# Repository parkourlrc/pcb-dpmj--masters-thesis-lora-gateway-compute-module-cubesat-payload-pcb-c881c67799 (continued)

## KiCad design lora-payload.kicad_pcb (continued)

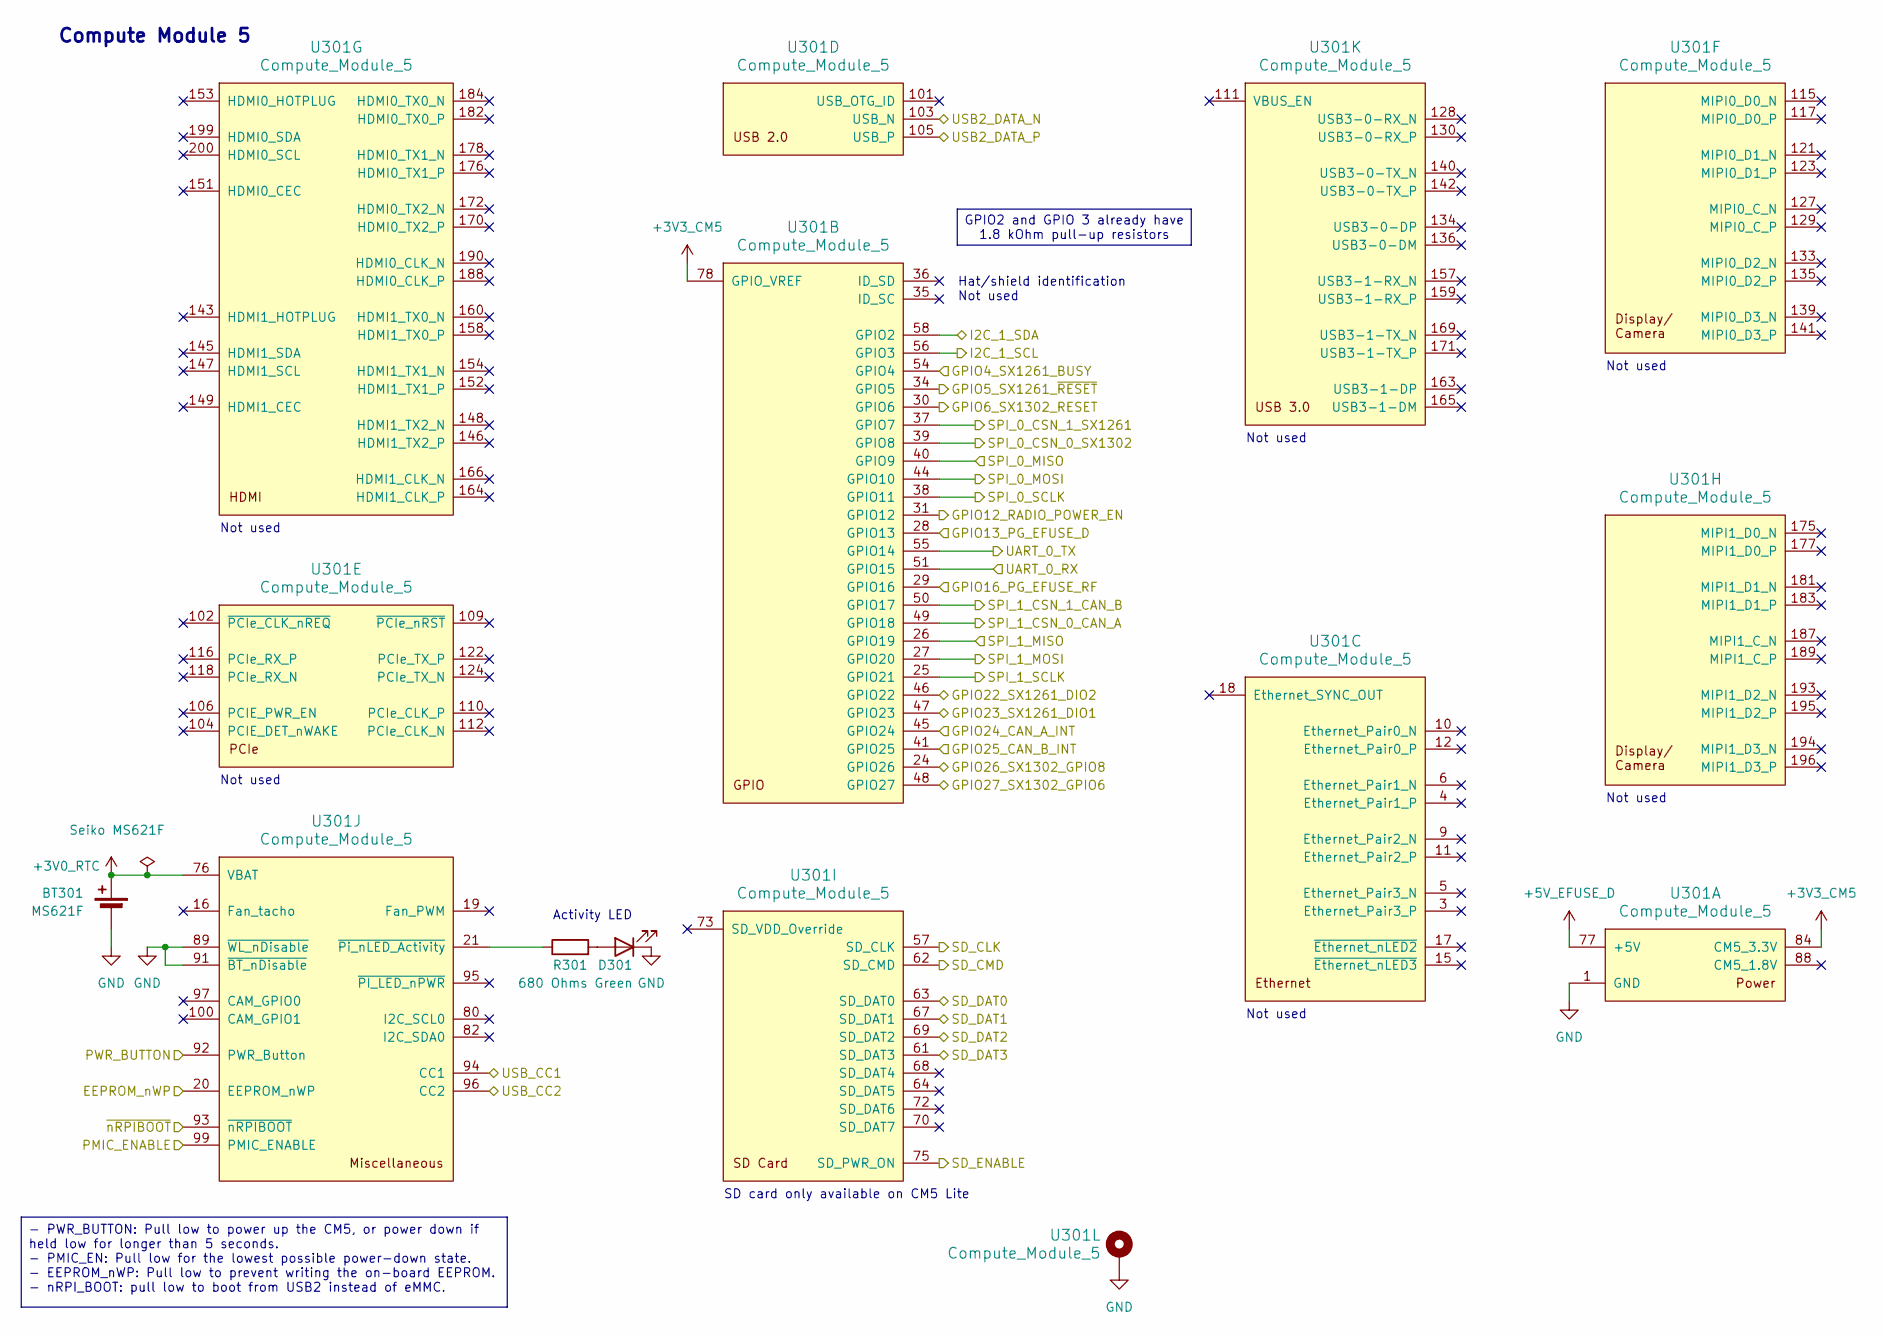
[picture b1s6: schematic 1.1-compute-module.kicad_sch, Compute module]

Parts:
BT301: Seiko MS621F; BatteryHolder_Seiko_MS621F; PartNumber MS621F
D301: Green; LED_0402_1005Metric
R301: 680 Ohms; R_0402_1005Metric
U301: Compute_Module_5; CM5

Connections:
+3V0_RTC: BT301.1 (+), U301.76 (VBAT)
+3V3_CM5: U301.78 (GPIO_VREF), U301.84 (CM5_3.3V), U301.86 (CM5_3.3V)
+5V_EFUSE_D: U301.77 (+5V), U301.79 (+5V), U301.81 (+5V), U301.83 (+5V), U301.85 (+5V), U301.87 (+5V); also elsewhere on the board
/1.0-digital/1.1-compute-module/EEPROM_nWP: U301.20 (EEPROM_nWP); also elsewhere on the board
/1.0-digital/1.1-compute-module/GPIO24_CAN_A_INT: U301.45 (GPIO24); also elsewhere on the board
/1.0-digital/1.1-compute-module/GPIO25_CAN_B_INT: U301.41 (GPIO25); also elsewhere on the board
/1.0-digital/1.1-compute-module/PMIC_ENABLE: U301.99 (PMIC_ENABLE); also elsewhere on the board
/1.0-digital/1.1-compute-module/SD_CLK: U301.57 (SD_CLK); also elsewhere on the board
/1.0-digital/1.1-compute-module/SD_CMD: U301.62 (SD_CMD); also elsewhere on the board
/1.0-digital/1.1-compute-module/SD_DAT0: U301.63 (SD_DAT0); also elsewhere on the board
/1.0-digital/1.1-compute-module/SD_DAT1: U301.67 (SD_DAT1); also elsewhere on the board
/1.0-digital/1.1-compute-module/SD_DAT2: U301.69 (SD_DAT2); also elsewhere on the board
/1.0-digital/1.1-compute-module/SD_DAT3: U301.61 (SD_DAT3); also elsewhere on the board
/1.0-digital/1.1-compute-module/SD_ENABLE: U301.75 (SD_PWR_ON); also elsewhere on the board
/1.0-digital/1.1-compute-module/SPI_1_CSN_0_CAN_A: U301.49 (GPIO18); also elsewhere on the board
/1.0-digital/1.1-compute-module/SPI_1_CSN_1_CAN_B: U301.50 (GPIO17); also elsewhere on the board
/1.0-digital/1.1-compute-module/SPI_1_MISO: U301.26 (GPIO19); also elsewhere on the board
/1.0-digital/1.1-compute-module/SPI_1_MOSI: U301.27 (GPIO20); also elsewhere on the board
/1.0-digital/1.1-compute-module/SPI_1_SCLK: U301.25 (GPIO21); also elsewhere on the board
/1.0-digital/1.1-compute-module/UART_0_RX: U301.51 (GPIO15); also elsewhere on the board
/1.0-digital/1.1-compute-module/UART_0_TX: U301.55 (GPIO14); also elsewhere on the board
/1.0-digital/1.1-compute-module/~nRPIBOOT: U301.93 (~nRPIBOOT); also elsewhere on the board
/1.0-digital/1.3-usb/USB2_DATA_N: U301.103 (USB_N); also elsewhere on the board
/1.0-digital/1.3-usb/USB2_DATA_P: U301.105 (USB_P); also elsewhere on the board
/1.0-digital/1.3-usb/USB_CC1: U301.94 (CC1); also elsewhere on the board
/1.0-digital/1.3-usb/USB_CC2: U301.96 (CC2); also elsewhere on the board
/1.0-digital/CM5_GPIO4_SX1261_BUSY: U301.54 (GPIO4); also elsewhere on the board
/1.0-digital/CM5_GPIO5_SX1261_~RESET: U301.34 (GPIO5); also elsewhere on the board
/1.0-digital/CM5_GPIO6_SX1302_RESET: U301.30 (GPIO6); also elsewhere on the board
/1.0-digital/CM5_GPIO12_RADIO_POWER_EN: U301.31 (GPIO12); also elsewhere on the board
/1.0-digital/CM5_GPIO22_SX1261_DIO2: U301.46 (GPIO22); also elsewhere on the board
/1.0-digital/CM5_GPIO23_SX1261_DIO1: U301.47 (GPIO23); also elsewhere on the board
/1.0-digital/CM5_GPIO26_SX1302_GPIO8: U301.24 (GPIO26); also elsewhere on the board
/1.0-digital/CM5_GPIO27_SX1302_GPIO6: U301.48 (GPIO27); also elsewhere on the board
/1.0-digital/CM5_SPI_0_CSN_0_SX1302: U301.39 (GPIO8); also elsewhere on the board
/1.0-digital/CM5_SPI_0_CSN_1_SX1261: U301.37 (GPIO7); also elsewhere on the board
/1.0-digital/CM5_SPI_0_MISO: U301.40 (GPIO9); also elsewhere on the board
/1.0-digital/CM5_SPI_0_MOSI: U301.44 (GPIO10); also elsewhere on the board
/1.0-digital/CM5_SPI_0_SCLK: U301.38 (GPIO11); also elsewhere on the board
/1.0-digital/I2C.SCL: U301.56 (GPIO3); also elsewhere on the board
/1.0-digital/I2C.SDA: U301.58 (GPIO2); also elsewhere on the board
/1.0-digital/PWR_BUTTON: U301.92 (PWR_Button); also elsewhere on the board
/3.0-power/3.1-efuse/PG_EFD: U301.28 (GPIO13); also elsewhere on the board
/3.0-power/3.1-efuse/PG_EFRF: U301.29 (GPIO16); also elsewhere on the board
GND: BT301.2 (-), D301.1 (K), U301.1 (GND), U301.2 (GND), U301.7 (GND), U301.8 (GND), U301.13 (GND), U301.14 (GND), U301.22 (GND), U301.23 (GND), U301.32 (GND), U301.33 (GND), U301.42 (GND), U301.43 (GND), U301.52 (GND), U301.53 (GND), U301.59 (GND), U301.60 (GND), U301.65 (GND), U301.66 (GND), U301.71 (GND), U301.74 (GND), U301.89 (~WL_nDisable), U301.91 (~BT_nDisable), U301.98 (GND), U301.107 (GND), U301.108 (GND), U301.113 (GND), U301.114 (GND), U301.119 (GND), U301.120 (GND), U301.125 (GND), U301.126 (GND), U301.131 (GND), U301.132 (GND), U301.137 (GND), U301.138 (GND), U301.144 (GND), U301.150 (GND), U301.155 (GND), U301.156 (GND), U301.161 (GND), U301.162 (GND), U301.167 (GND), U301.168 (GND), U301.173 (GND), U301.174 (GND), U301.179 (GND), U301.180 (GND), U301.185 (GND), U301.186 (GND), U301.191 (GND), U301.192 (GND), U301.197 (GND), U301.198 (GND), U301.MH; also elsewhere on the board
unnamed: D301.2 (A), R301.2
unnamed: R301.1, U301.21 (~Pi_nLED_Activity)

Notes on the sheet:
SD card only available on CM5 Lite
Compute Module 5
Not used
Hat/shield identification Not used
Activity LED
- PWR_BUTTON: Pull low to power up the CM5, or power down if held low for longer than 5 seconds. - PMIC_EN: Pull low for the lowest possible power-down state. - EEPROM_nWP: Pull low to prevent writing the on-board EEPROM. - nRPI_BOOT: pull low to boot from USB2 instead of eMMC.
GPIO2 and GPIO 3 already have 1.8 kOhm pull-up resistors

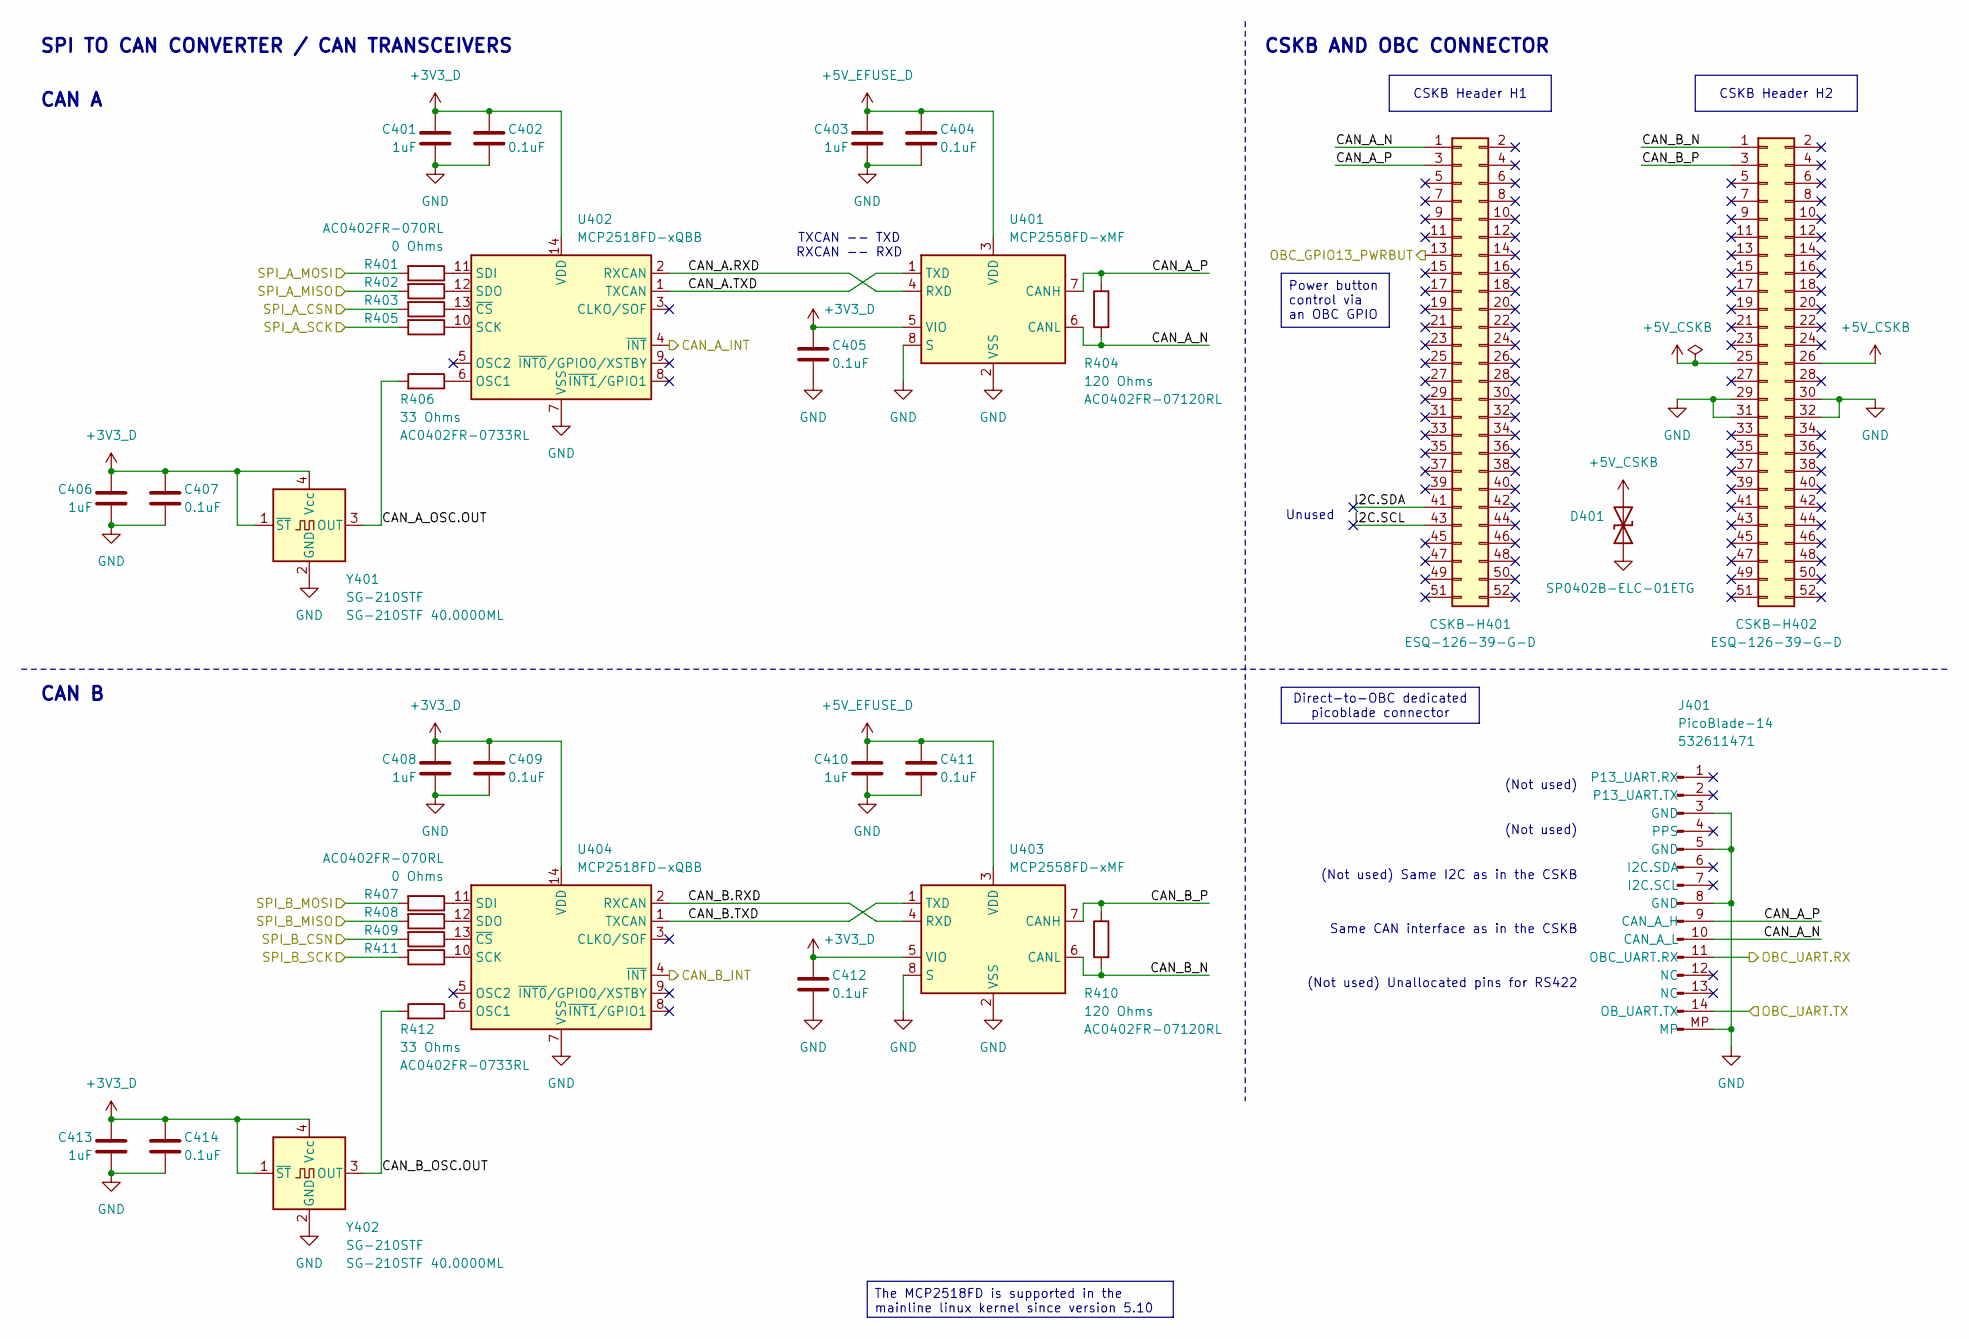
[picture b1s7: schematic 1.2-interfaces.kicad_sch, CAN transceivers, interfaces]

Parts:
C401, C403, C406, C408, C410, C413: 1uF; C_0402_1005Metric; PartNumber GRM155Z71A105KE01J
C402, C404, C405, C407, C409, C411, C412, C414: 0.1uF; C_0402_1005Metric; PartNumber GRM155R71C104KA88J
CSKB-H401, CSKB-H402: Conn_02x26_Odd_Even; PinHeader_2x26_P2.54mm_Vertical_ESQ-126-39-X-D; PartNumber ESQ-126-39-G-D
D401: SP0402B-ELC-01ETG; D_SOD-882; PartNumber SP0402B-ELC-01ETG
J401: PicoBlade-14; Molex_PicoBlade_53261-1471_1x14-1MP_P1.25mm_Horizontal; PartNumber 532611471
R401, R402, R403, R407, R408, R409: 100 Ohms; R_0402_1005Metric; PartNumber AC0402FR-070RL
R404, R410: 120 Ohms; R_0402_1005Metric; PartNumber AC0402FR-07120RL
R405, R411: 0 Ohms; R_0402_1005Metric; PartNumber AC0402FR-070RL
R406, R412: 33 Ohms; R_0402_1005Metric; PartNumber AC0402FR-0733RL
U401, U403: MCP2558FD-xMF; DFN-8-1EP_3x3mm_P0.65mm_EP1.55x2.4mm
U402, U404: MCP2518FD-xQBB; DFN-14-1EP_3x4.5mm_P0.65mm_EP1.65x4.25mm
Y401, Y402: SG-210STF; Oscillator_SMD_SeikoEpson_SG210-4Pin_2.5x2.0mm; PartNumber SG-210STF 40.0000ML

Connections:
+3V3_D: C401.2, C402.2, C405.2, C406.2, C407.2, C408.2, C409.2, C412.2, C413.2, C414.2, U401.5 (VIO), U402.14 (VDD), U403.5 (VIO), U404.14 (VDD), Y401.1 (~ST), Y401.4 (Vcc), Y402.1 (~ST), Y402.4 (Vcc); also elsewhere on the board
+5V_CSKB: CSKB-H402.25, CSKB-H402.26, D401.2 (A2); also elsewhere on the board
+5V_EFUSE_D: C403.2, C404.2, C410.2, C411.2, U401.3 (VDD), U403.3 (VDD); also elsewhere on the board
/1.0-digital/1.1-compute-module/GPIO24_CAN_A_INT: U402.4 (~INT); also elsewhere on the board
/1.0-digital/1.1-compute-module/GPIO25_CAN_B_INT: U404.4 (~INT); also elsewhere on the board
/1.0-digital/1.1-compute-module/SPI_1_CSN_0_CAN_A: R403.2; also elsewhere on the board
/1.0-digital/1.1-compute-module/SPI_1_CSN_1_CAN_B: R409.2; also elsewhere on the board
/1.0-digital/1.1-compute-module/SPI_1_MISO: R402.2, R408.2; also elsewhere on the board
/1.0-digital/1.1-compute-module/SPI_1_MOSI: R401.2, R407.2; also elsewhere on the board
/1.0-digital/1.1-compute-module/SPI_1_SCLK: R405.2, R411.2; also elsewhere on the board
/1.0-digital/1.1-compute-module/UART_0_RX: J401.11 (OBC_UART.RX); also elsewhere on the board
/1.0-digital/1.1-compute-module/UART_0_TX: J401.14 (OB_UART.TX); also elsewhere on the board
/1.0-digital/1.2-interfaces/CAN_A.RXD: U401.4 (RXD), U402.2 (RXCAN)
/1.0-digital/1.2-interfaces/CAN_A.TXD: U401.1 (TXD), U402.1 (TXCAN)
/1.0-digital/1.2-interfaces/CAN_A_N: CSKB-H401.1, J401.10 (CAN_A_L), R404.2, U401.6 (CANL)
/1.0-digital/1.2-interfaces/CAN_A_OSC.OUT: R406.2, Y401.3 (OUT)
/1.0-digital/1.2-interfaces/CAN_A_P: CSKB-H401.3, J401.9 (CAN_A_H), R404.1, U401.7 (CANH)
/1.0-digital/1.2-interfaces/CAN_B.RXD: U403.4 (RXD), U404.2 (RXCAN)
/1.0-digital/1.2-interfaces/CAN_B.TXD: U403.1 (TXD), U404.1 (TXCAN)
/1.0-digital/1.2-interfaces/CAN_B_N: CSKB-H402.1, R410.2, U403.6 (CANL)
/1.0-digital/1.2-interfaces/CAN_B_OSC.OUT: R412.2, Y402.3 (OUT)
/1.0-digital/1.2-interfaces/CAN_B_P: CSKB-H402.3, R410.1, U403.7 (CANH)
/1.0-digital/1.2-interfaces/I2C.SCL: CSKB-H401.43
/1.0-digital/1.2-interfaces/I2C.SDA: CSKB-H401.41
/1.0-digital/PWR_BUTTON: CSKB-H401.13; also elsewhere on the board
GND: C401.1, C402.1, C403.1, C404.1, C405.1, C406.1, C407.1, C408.1, C409.1, C410.1, C411.1, C412.1, C413.1, C414.1, CSKB-H402.29, CSKB-H402.30, CSKB-H402.31, CSKB-H402.32, D401.1 (A1), J401.3 (GND), J401.5 (GND), J401.8 (GND), J401.MP, U401.2 (VSS), U401.8 (S), U401.9 (VSS), U402.7 (VSS), U402.15 (VSS), U403.2 (VSS), U403.8 (S), U403.9 (VSS), U404.7 (VSS), U404.15 (VSS), Y401.2 (GND), Y402.2 (GND); also elsewhere on the board
unnamed: R406.1, U402.6 (OSC1)
unnamed: R405.1, U402.10 (SCK)
unnamed: R401.1, U402.11 (SDI)
unnamed: R402.1, U402.12 (SDO)
unnamed: R403.1, U402.13 (~CS)
unnamed: R412.1, U404.6 (OSC1)
unnamed: R411.1, U404.10 (SCK)
unnamed: R407.1, U404.11 (SDI)
unnamed: R408.1, U404.12 (SDO)
unnamed: R409.1, U404.13 (~CS)

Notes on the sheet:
(Not used) Same I2C as in the CSKB
(Not used) Unallocated pins for RS422
(Not used)
Same CAN interface as in the CSKB
CAN B
TXCAN -- TXD RXCAN -- RXD
CSKB AND OBC CONNECTOR
CAN A
Unused
SPI TO CAN CONVERTER / CAN TRANSCEIVERS
The MCP2518FD is supported in the mainline linux kernel since version 5.10
Direct-to-OBC dedicated picoblade connector
CSKB Header H1
CSKB Header H2
Power button control via an OBC GPIO

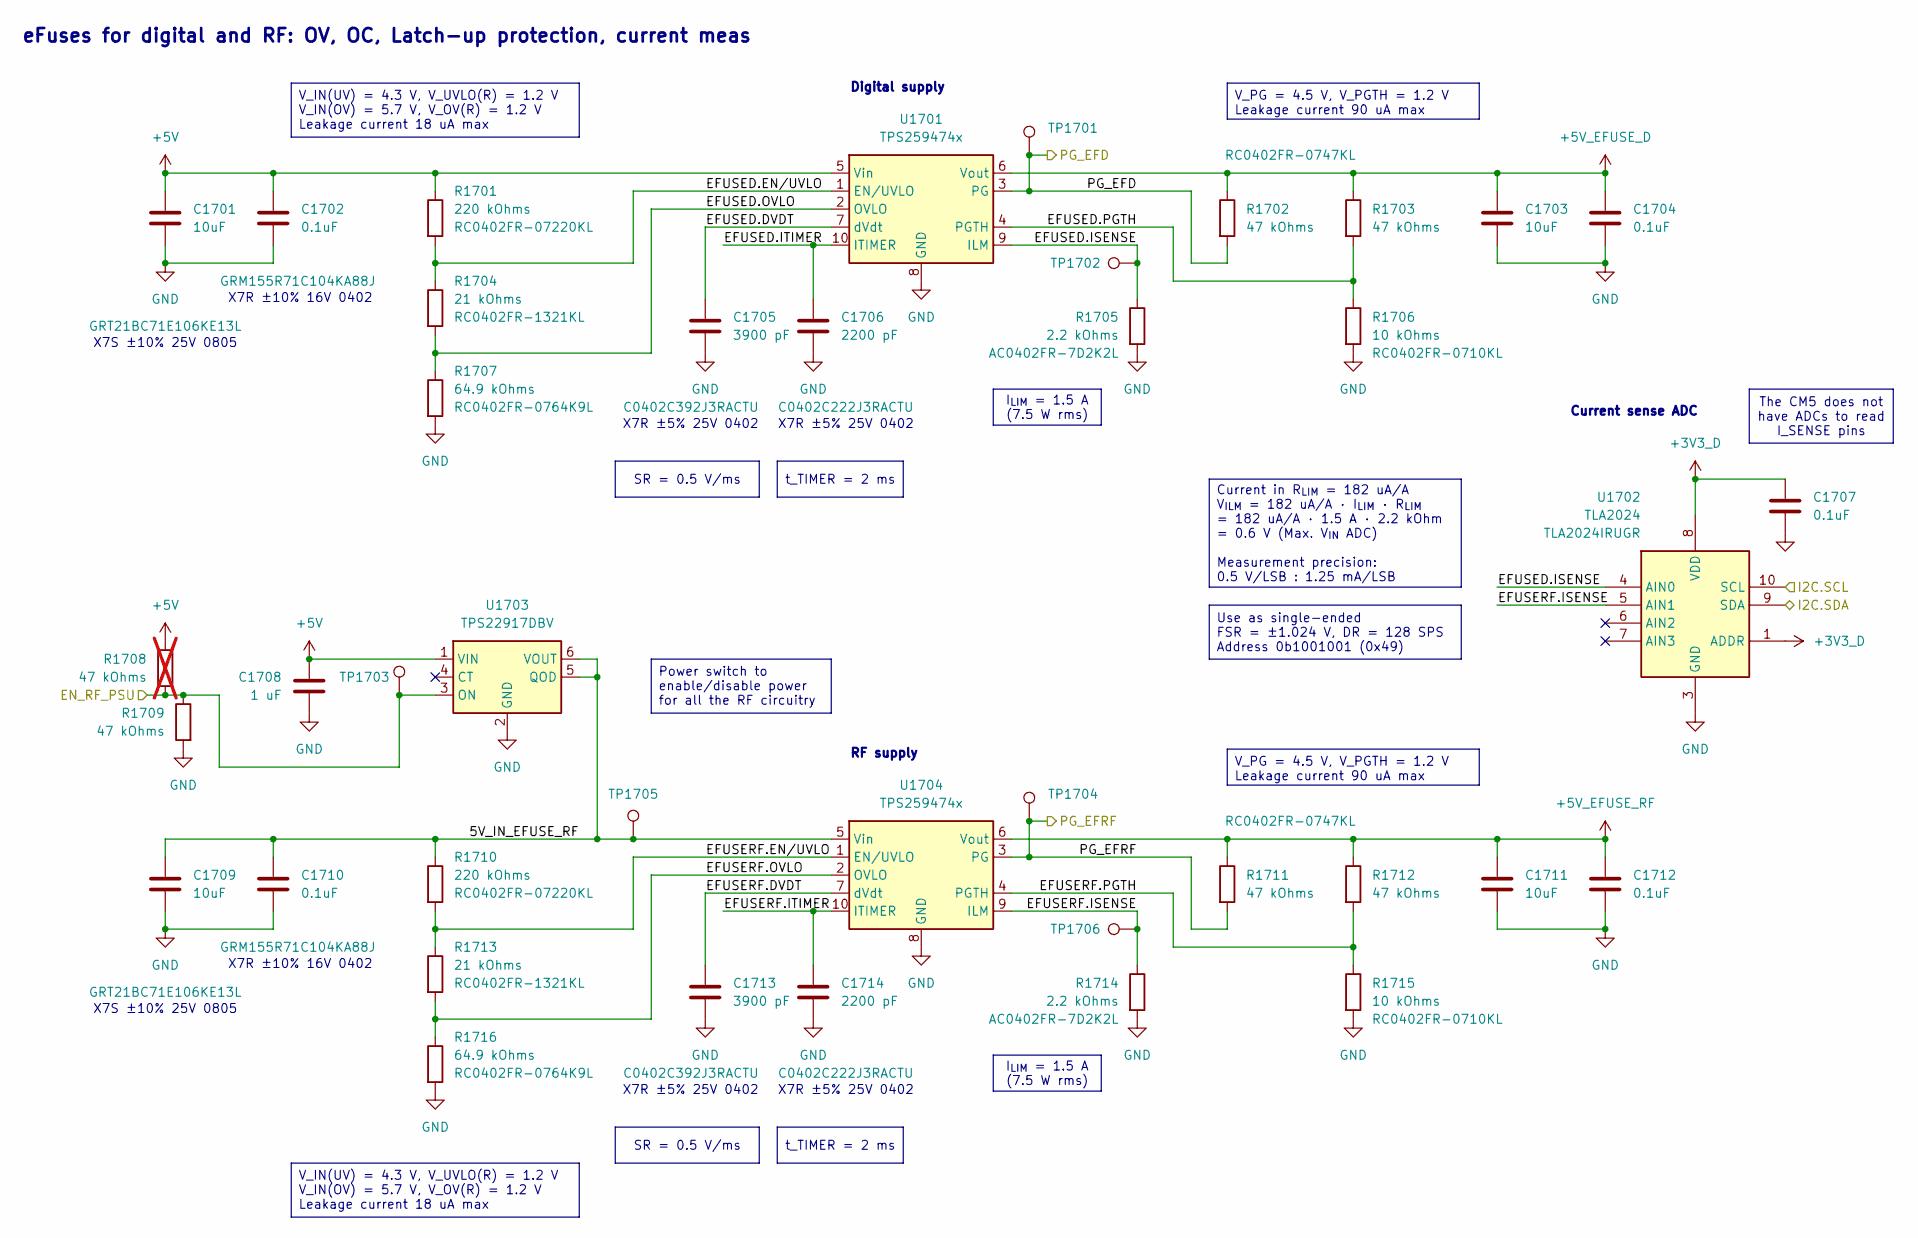
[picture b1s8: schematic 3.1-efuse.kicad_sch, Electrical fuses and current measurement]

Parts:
C1701, C1703, C1709, C1711: 10uF; C_0805_2012Metric; PartNumber GRT21BC71E106KE13L
C1702, C1704, C1707, C1710, C1712: 0.1uF; C_0402_1005Metric; PartNumber GRM155R71C104KA88J
C1705, C1713: 3900 pF; C_0402_1005Metric; PartNumber C0402C392J3RACTU
C1706, C1714: 2200 pF; C_0402_1005Metric; PartNumber C0402C222J3RACTU
C1708: 1 uF; C_0402_1005Metric; PartNumber GRM155Z71A105KE01J
R1701, R1710: 220 kOhms; R_0402_1005Metric; PartNumber RC0402FR-07220KL
R1702, R1703, R1709, R1711, R1712: 47 kOhms; R_0402_1005Metric; PartNumber RC0402FR-0747KL
R1704, R1713: 21 kOhms; R_0402_1005Metric; PartNumber RC0402FR-1321KL
R1705, R1714: 2.2 kOhms; R_0402_1005Metric; PartNumber AC0402FR-7D2K2L
R1706, R1715: 10 kOhms; R_0402_1005Metric; PartNumber RC0402FR-0710KL
R1707, R1716: 64.9 kOhms; R_0402_1005Metric; PartNumber RC0402FR-0764K9L
R1708: 47 kOhms; R_0402_1005Metric; PartNumber RC0402FR-0747KL; not fitted
TP1701, TP1702, TP1703, TP1704, TP1705, TP1706: TestPoint; TestPoint_Pad_D1.0mm
U1701, U1704: TPS259474x; Texas_VQFN-10-HR_2x2_Pitch0.45mm
U1702: TLA2024; Texas_X2QFN-10_1.5x2.00mm_Pitch0.5mm; PartNumber TLA2024IRUGR
U1703: TPS22917DBV; SOT-23-6

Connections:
+3V3_D: C1707.2, U1702.1 (ADDR), U1702.8 (VDD); also elsewhere on the board
+5V: C1701.2, C1702.2, C1708.2, R1701.1, R1708.1, U1701.5 (Vin), U1703.1 (VIN); also elsewhere on the board
+5V_EFUSE_D: C1703.2, C1704.2, R1702.1, R1703.1, U1701.6 (Vout); also elsewhere on the board
+5V_EFUSE_RF: C1711.2, C1712.2, R1711.1, R1712.1, U1704.6 (Vout); also elsewhere on the board
/1.0-digital/CM5_GPIO12_RADIO_POWER_EN: R1708.2, R1709.1, TP1703.1, U1703.3 (ON); also elsewhere on the board
/1.0-digital/I2C.SCL: U1702.10 (SCL); also elsewhere on the board
/1.0-digital/I2C.SDA: U1702.9 (SDA); also elsewhere on the board
/3.0-power/3.1-efuse/5V_IN_EFUSE_RF: C1709.2, C1710.2, R1710.1, TP1705.1, U1703.5 (QOD), U1703.6 (VOUT), U1704.5 (Vin)
/3.0-power/3.1-efuse/EFUSED.DVDT: C1705.2, U1701.7 (dVdt)
/3.0-power/3.1-efuse/EFUSED.EN/UVLO: R1701.2, R1704.1, U1701.1 (EN/UVLO)
/3.0-power/3.1-efuse/EFUSED.ISENSE: R1705.1, TP1702.1, U1701.9 (ILM), U1702.4 (AIN0)
/3.0-power/3.1-efuse/EFUSED.ITIMER: C1706.2, U1701.10 (ITIMER)
/3.0-power/3.1-efuse/EFUSED.OVLO: R1704.2, R1707.1, U1701.2 (OVLO)
/3.0-power/3.1-efuse/EFUSED.PGTH: R1703.2, R1706.1, U1701.4 (PGTH)
/3.0-power/3.1-efuse/EFUSERF.DVDT: C1713.2, U1704.7 (dVdt)
/3.0-power/3.1-efuse/EFUSERF.EN/UVLO: R1710.2, R1713.1, U1704.1 (EN/UVLO)
/3.0-power/3.1-efuse/EFUSERF.ISENSE: R1714.1, TP1706.1, U1702.5 (AIN1), U1704.9 (ILM)
/3.0-power/3.1-efuse/EFUSERF.ITIMER: C1714.2, U1704.10 (ITIMER)
/3.0-power/3.1-efuse/EFUSERF.OVLO: R1713.2, R1716.1, U1704.2 (OVLO)
/3.0-power/3.1-efuse/EFUSERF.PGTH: R1712.2, R1715.1, U1704.4 (PGTH)
/3.0-power/3.1-efuse/PG_EFD: R1702.2, TP1701.1, U1701.3 (PG); also elsewhere on the board
/3.0-power/3.1-efuse/PG_EFRF: R1711.2, TP1704.1, U1704.3 (PG); also elsewhere on the board
GND: C1701.1, C1702.1, C1703.1, C1704.1, C1705.1, C1706.1, C1707.1, C1708.1, C1709.1, C1710.1, C1711.1, C1712.1, C1713.1, C1714.1, R1705.2, R1706.2, R1707.2, R1709.2, R1714.2, R1715.2, R1716.2, U1701.8 (GND), U1702.3 (GND), U1703.2 (GND), U1704.8 (GND); also elsewhere on the board

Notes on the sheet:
X7R ±5% 25V 0402
X7R ±10% 16V 0402
eFuses for digital and RF: OV, OC, Latch-up protection, current meas
X7S ±10% 25V 0805
RF supply
Current sense ADC
Digital supply
t_TIMER = 2 ms
V_IN(UV) = 4.3 V, V_UVLO(R) = 1.2 V V_IN(OV) = 5.7 V, V_OV(R) = 1.2 V Leakage current 18 uA max
Current in R_{LIM} = 182 uA/A V_{ILM} = 182 uA/A · I_{LIM} · R_{LIM} = 182 uA/A · 1.5 A · 2.2 kOhm = 0.6 V (Max. V_{IN} ADC) Measurement precision: 0.5 V/LSB : 1.25 mA/LSB
I_{LIM} = 1.5 A (7.5 W rms)
Use as single-ended FSR = ±1.024 V, DR = 128 SPS Address 0b1001001 (0x49)
SR = 0.5 V/ms
The CM5 does not have ADCs to read I_SENSE pins
V_PG = 4.5 V, V_PGTH = 1.2 V Leakage current 90 uA max
Power switch to enable/disable power for all the RF circuitry

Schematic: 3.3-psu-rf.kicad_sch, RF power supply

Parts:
C1901, C1916, C1921: 10uF; C_0805_2012Metric; PartNumber GRT21BC71E106KE13L
C1902: 2200pF; C_0402_1005Metric; PartNumber C0402C222J3RACTU
C1903, C1912, C1914, C1918, C1923, C1924: 0.1uF; C_0402_1005Metric; PartNumber GRM155R71C104KA88J
C1904, C1905, C1907, C1908, C1909: 22uF; C_0805_2012Metric; PartNumber CL21A226KOQNNNG
C1906: 47uF; C_0805_2012Metric; PartNumber GRM21BR61A476ME15K
C1910: 0.47 uF; C_0402_1005Metric; PartNumber CGA2B1X7S1C474K050BC
C1911, C1915, C1917, C1920, C1922, C1925: 1uF; C_0402_1005Metric; PartNumber GRM155Z71A105KE01J
C1913: 10 nF; C_0402_1005Metric; PartNumber GCM155R71E103KA37J
C1919: 0.1 uF; C_0402_1005Metric; PartNumber GRM155R71C104KA88J
FB1901: 8.5 Ohms @ 100 MHz; L_0603_1608Metric; PartNumber BLE18PS080SN1D
L1901: 2.2 uH; L_Bourns-SRN4018; PartNumber SRN4018-2R2M
R1901: 16.9 kOhms; R_0402_1005Metric; PartNumber AC0402FR-0716K9L
R1902, R1906: 4.87 kOhms; R_0402_1005Metric; PartNumber RC0402FR-074K87L
R1903: 42.2 kOhms; R_0402_1005Metric; PartNumber RC0402FR-0742K2L
R1904, R1907, R1908: 47 kOhms; R_0402_1005Metric; PartNumber RC0402FR-0747KL
R1905: 12.1 kOhms; R_0402_1005Metric; PartNumber AC0402FR-0712K1L
TP1901, TP1902: TestPoint; TestPoint_Pad_D1.0mm
U1901: TPS62912; Texas_RPU0010A_VQFN-HR-10_2x2mm_P0.5mm
U1902: TPS73601DBV; SOT-23-5
U1903: LP5912-3.3DRV; WSON-6-1EP_2x2mm_P0.65mm_EP1x1.6mm
U1904: LP5912-1.8DRV; WSON-6-1EP_2x2mm_P0.65mm_EP1x1.6mm

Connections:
+1V8_RF: C1924.2, C1925.2, TP1902.1, U1904.1 (OUT); also elsewhere on the board
+3V3_D: R1904.2, R1907.2, R1908.2; also elsewhere on the board
+3V3_RF: C1919.2, C1920.2, C1921.2, U1903.1 (OUT); also elsewhere on the board
+3V6_RF: C1907.2, C1908.2, C1909.2, C1917.2, C1918.2, C1922.2, C1923.2, FB1901.2, R1901.1, U1903.6 (IN), U1904.6 (IN); also elsewhere on the board
+4V2_RF: C1913.2, C1914.2, C1915.2, C1916.2, R1905.1, U1902.5 (OUT); also elsewhere on the board
+5V_EFUSE_RF: C1901.2, C1902.2, C1911.2, C1912.2, U1901.6 (VIN), U1902.1 (IN); also elsewhere on the board
/3.0-power/3.1-efuse/PG_EFRF: U1901.1 (EN/SYNC), U1902.3 (EN); also elsewhere on the board
/3.0-power/3.3-psu-rf/DC3V6RF.FB: R1901.2, R1902.1, U1901.9 (FB)
/3.0-power/3.3-psu-rf/DC3V6RF.NR/SS: C1910.2, U1901.8 (NR/SS)
/3.0-power/3.3-psu-rf/DC3V6RF.SCONF: R1903.2, U1901.10 (S-CONF)
/3.0-power/3.3-psu-rf/DC3V6RF.SW: L1901.1, U1901.2 (SW)
/3.0-power/3.3-psu-rf/DC3V6RF.VO: C1903.2, C1904.2, C1905.2, C1906.2, FB1901.1, L1901.2, U1901.3 (VO)
/3.0-power/3.3-psu-rf/PG_3V6RF: R1904.1, TP1901.1, U1901.5 (PG), U1903.4 (EN), U1904.4 (EN)
/3.0-power/PG_1V8RF: R1908.1, U1904.3 (PG)
/3.0-power/PG_3V3RF: R1907.1, U1903.3 (PG)
GND: C1901.1, C1902.1, C1903.1, C1904.1, C1905.1, C1906.1, C1907.1, C1908.1, C1909.1, C1910.1, C1911.1, C1912.1, C1914.1, C1915.1, C1916.1, C1917.1, C1918.1, C1919.1, C1920.1, C1921.1, C1922.1, C1923.1, C1924.1, C1925.1, R1902.2, R1903.1, R1906.2, U1901.4 (PGND), U1901.7 (PSNS), U1902.2 (GND), U1903.5 (GND), U1903.7 (EP), U1904.5 (GND), U1904.7 (EP); also elsewhere on the board
unnamed: C1913.1, R1905.2, R1906.1, U1902.4 (FB)

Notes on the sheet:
Low-DropOut regulators
X7S ±10% 16V 0402
E96 1%
X7S ±10% 25V 0805
44mOhm ±20% 2.9A
X5R ±10% 16V 0805
Low-noise DC/DC converters
X7R ±10% 25V 0402
X7R ±5% 25V 0402
X7R ±10% 16V 0402
4mOhm 8A
X5R ±20% 10V 0805
V_{N} = 36 µVrms (10Hz-100kHz)
V_{N} = 25 µVrms (100Hz-100kHz)
Enabled if the eFuse asserts PG
V_{DO} = 3.6 V - 1.8 V = 1.8 V I_{CC} = 2 mA (TG2520SMN datasheet) P_{D} = V_{DO} * I_{CC} = 4 mW
V_{N} = 12 µVrms (10Hz-100kHz)
S-CONF to 42.2 kOhm resistor: - F_{SW} = 2.2 MHz - Spread spectrum random - Output discharge ON - Sync OFF
Extra bypass capacitors for noise filtering (vs digital DC/DCs). Added a 47 uF and a 22 uF cap as recommended
Activates 1V8 and 3V3 supply
V_{DO} = 5 V - 4.2 V = 0.8 V I_{CC} = 53 mA (QPL9095 datasheet) P_{D} = V_{DO} * I_{CC} = 42 mW
Up to 2 A
V_{DO} = 3.6 V - 3.3 V = 0.3 V I_{CC} = 200 mA (max, aprox) P_{D} = V_{DO} * I_{CC} = 60 mW

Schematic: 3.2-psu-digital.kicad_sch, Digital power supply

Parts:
C1801, C1810: 10uF; C_0805_2012Metric; PartNumber GRT21BC71E106KE13L
C1802, C1811: 2200pF; C_0402_1005Metric; PartNumber C0402C222J3RACTU
C1803, C1812: 0.1uF; C_0402_1005Metric; PartNumber GRM155R71C104KA88J
C1804, C1805, C1806, C1807, C1808, C1813, C1814, C1815, C1816, C1817: 22uF; C_0805_2012Metric; PartNumber CL21A226KOQNNNG
C1809, C1818: 0.47 uF; C_0402_1005Metric; PartNumber CGA2B1X7S1C474K050BC
FB1801, FB1802: 8.5 Ohms @ 100 MHz; L_0603_1608Metric; PartNumber BLE18PS080SN1D
L1801, L1802: 2.2 uH; L_Bourns-SRN4018; PartNumber SRN4018-2R2M
R1801: 15.4 kOhms; R_0402_1005Metric; PartNumber RC0402FR-0715K4L
R1802, R1806: 4.87 kOhms; R_0402_1005Metric; PartNumber RC0402FR-074K87L
R1803, R1807: 42.2 kOhms; R_0402_1005Metric; PartNumber RC0402FR-0742K2L
R1804: 47 kOhms; R_0402_1005Metric; PartNumber RC0402FR-0747KL; not fitted
R1805: 2.49 kOhms; R_0402_1005Metric; PartNumber RC0402FR-072K49L
R1808: 47 kOhms; R_0402_1005Metric; PartNumber RC0402FR-0747KL
TP1801, TP1802, TP1803: TestPoint; TestPoint_Pad_D1.0mm
U1801, U1802: TPS62912; Texas_RPU0010A_VQFN-HR-10_2x2mm_P0.5mm

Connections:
+1V2_D: C1816.2, C1817.2, FB1802.2, R1805.1, R1808.2, TP1802.1; also elsewhere on the board
+3V3_D: C1807.2, C1808.2, FB1801.2, R1801.1, R1804.2; also elsewhere on the board
+5V_EFUSE_D: C1801.2, C1802.2, C1810.2, C1811.2, U1801.6 (VIN), U1802.6 (VIN); also elsewhere on the board
/3.0-power/3.1-efuse/PG_EFD: U1802.1 (EN/SYNC); also elsewhere on the board
/3.0-power/3.2-psu-digital/DC1V2.NR/SS: C1818.2, U1802.8 (NR/SS)
/3.0-power/3.2-psu-digital/DC1V2.SCONF: R1807.2, U1802.10 (S-CONF)
/3.0-power/3.2-psu-digital/DC1V2D.FB: R1805.2, R1806.1, U1802.9 (FB)
/3.0-power/3.2-psu-digital/DC1V2D.SW: L1802.1, U1802.2 (SW)
/3.0-power/3.2-psu-digital/DC1V2D.VO: C1812.2, C1813.2, C1814.2, C1815.2, FB1802.1, L1802.2, U1802.3 (VO)
/3.0-power/3.2-psu-digital/DC3V3D.FB: R1801.2, R1802.1, U1801.9 (FB)
/3.0-power/3.2-psu-digital/DC3V3D.NR/SS: C1809.2, U1801.8 (NR/SS)
/3.0-power/3.2-psu-digital/DC3V3D.SCONF: R1803.2, U1801.10 (S-CONF)
/3.0-power/3.2-psu-digital/DC3V3D.SW: L1801.1, U1801.2 (SW)
/3.0-power/3.2-psu-digital/DC3V3D.VO: C1803.2, C1804.2, C1805.2, C1806.2, FB1801.1, L1801.2, U1801.3 (VO)
/3.0-power/3.2-psu-digital/PG_1V2D: R1808.1, TP1803.1, U1801.1 (EN/SYNC), U1802.5 (PG)
/3.0-power/PG_3V3D: R1804.1, TP1801.1, U1801.5 (PG)
GND: C1801.1, C1802.1, C1803.1, C1804.1, C1805.1, C1806.1, C1807.1, C1808.1, C1809.1, C1810.1, C1811.1, C1812.1, C1813.1, C1814.1, C1815.1, C1816.1, C1817.1, C1818.1, R1802.2, R1803.1, R1806.2, R1807.1, U1801.4 (PGND), U1801.7 (PSNS), U1802.4 (PGND), U1802.7 (PSNS); also elsewhere on the board

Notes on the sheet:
E96 1%
X7S ±10% 16V 0402
X5R ±10% 16V 0805
44mOhm ±20% 2.9A
Not used
X7R ±10% 16V 0402
X7S ±10% 25V 0805
X7R ±5% 25V 0402
4mOhm 8A
Power supply for digital: Low-noise DC/DC converters
V_{H} >= 1.04 V
EN/SYNC pin: Open-drain, internal 500 kOhm pull-down. PG1V2 with 47 kOhm pull-up to 1V2 rail (instead of 5V) to perform a sequential power-up (first 1V2, second 3V3, see note below)
Always enabled
Activates 3V3 supply after the 1V2
S-CONF to 42.2 kOhm resistor: - F_{SW} = 2.2 MHz - Spread spectrum random - Output discharge ON - Sync OFF
The TPS62912 PG pin is in high Z when V(FB) >= 95%, and driven low when V(FB) <= 90% . The open-drain pin requires a pullup. The PG signal is used for sequencing of multiple rails by connecting to the EN pin of other converters. To ensure control of all digital IOs during the power-up/down of the S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
